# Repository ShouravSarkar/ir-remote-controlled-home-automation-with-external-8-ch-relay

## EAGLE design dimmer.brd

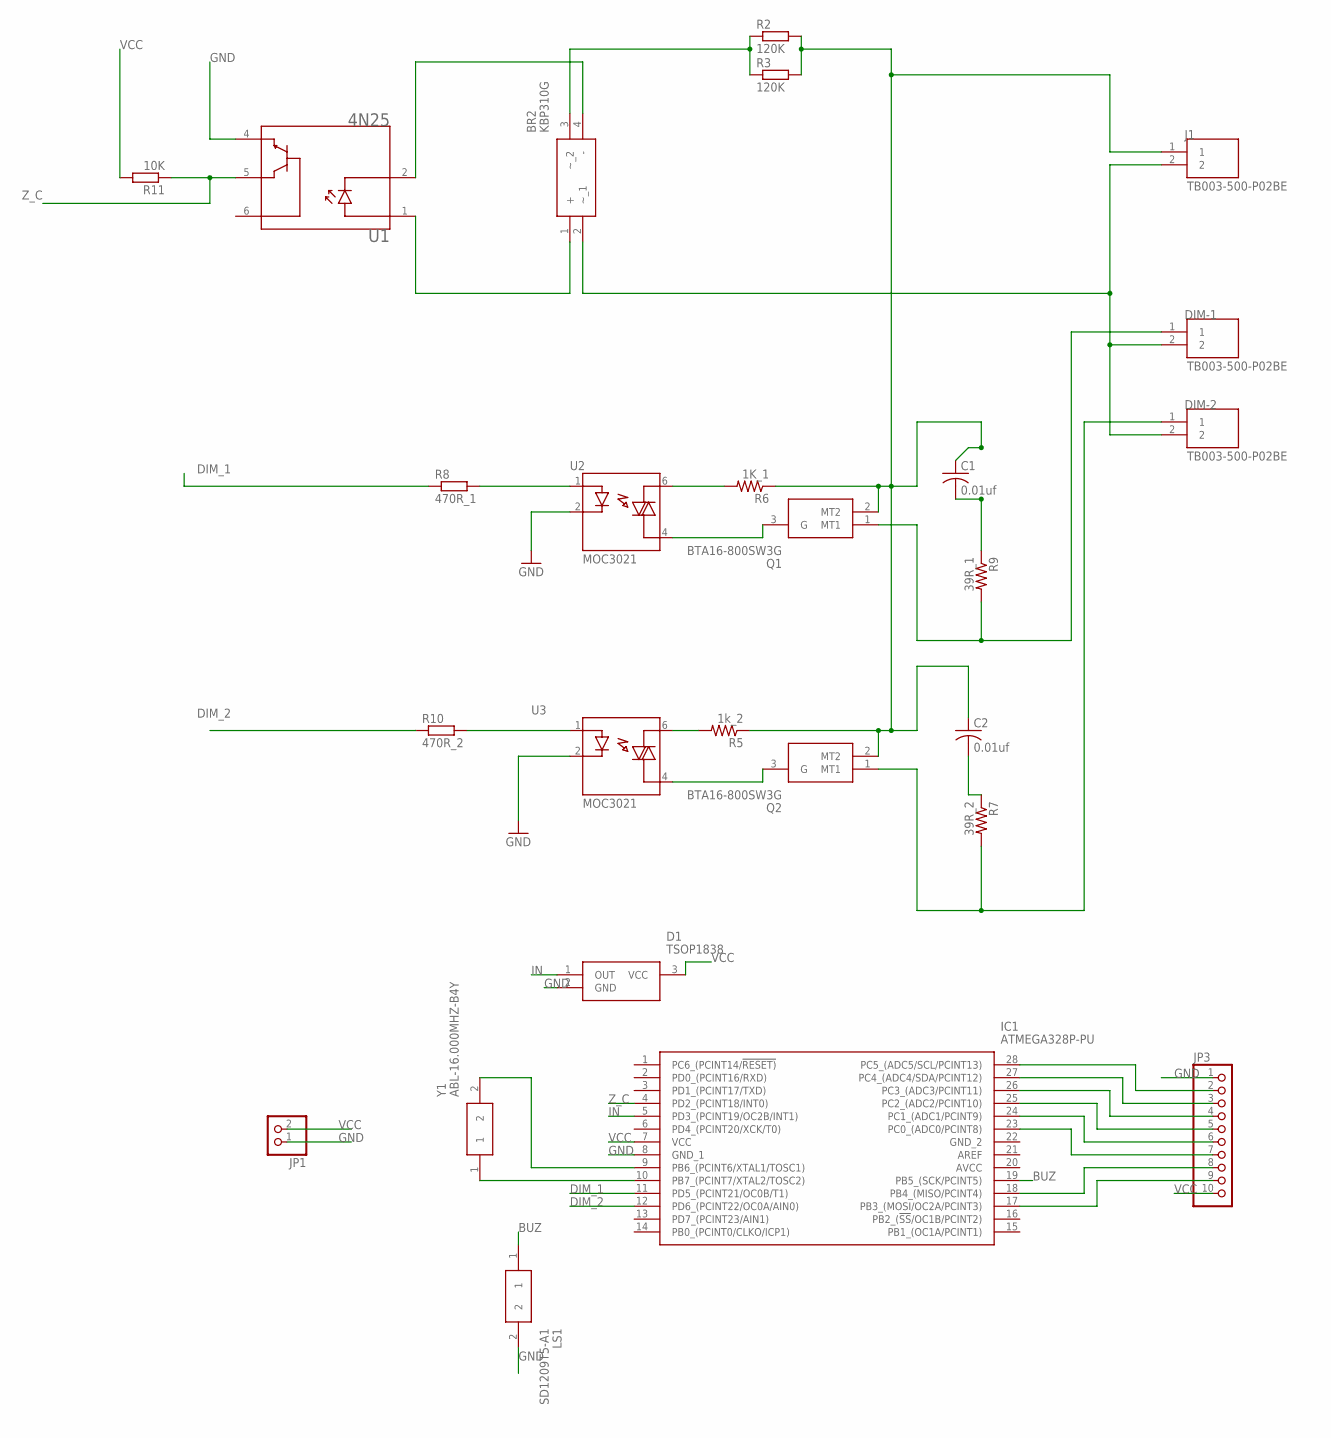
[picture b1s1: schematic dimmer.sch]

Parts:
BR2: KBP310G; TO385P508X1473X1168-4P
C1, C2: 0.01uf; C150-072X183
D1: TSOP1838; TSOP4856
DIM-1, DIM-2: TB003-500-P02BE; CUI_TB003-500-P02BE
IC1: ATMEGA328P-PU; DIP794W53P254L3467H457Q28N
J1: TB003-500-P02BE; CUI_TB003-500-P02BE
JP1: PINHD-1X2; 1X02
JP3: PINHD-1X10; 1X10
LS1: SD1209T5-A1
Q1, Q2: BTA16-800SW3G; TO254P482X997X2018-3P
R2, R3: 120K; 0617/22
R5: 1k_2; 0309/12
R6: 1K_1; 0309/12
R7: 39R_2; 0309/12
R8: 470R_1; 0207/10
R9: 39R_1; 0309/12
R10: 470R_2; 0207/10
R11: 10K; 0207/10
U1: 4N25; DIP762W50P254L712H400Q6N
U2, U3: MOC3021; DIP762W45P254L889H508Q6
Y1: ABL-16.000MHZ-B4Y; HC/49US_(AT49)PTH

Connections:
BUZ: IC1.19 (PB5_(SCK/PCINT5)), LS1.1
DIM_1: IC1.11 (PD5_(PCINT21/OC0B/T1)), R8.1
DIM_2: IC1.12 (PD6_(PCINT22/OC0A/AIN0)), R10.1
GND: D1.2 (GND), IC1.8 (GND_1), JP1.1, JP3.1, LS1.2, U1.4 (E), U2.2 (CATODE), U3.2 (CATODE)
IN: D1.1 (OUT), IC1.5 (PD3_(PCINT19/OC2B/INT1))
unnamed: BR2.4 (-), U1.2 (K)
unnamed: BR2.1 (+), U1.1 (A)
unnamed: BR2.3 (~_2), R2.1, R3.1
unnamed: R10.2, U3.1 (ANODE)
unnamed: C2.2, R7.1
unnamed: BR2.2 (~_1), DIM-1.2, DIM-2.2, J1.2
unnamed: IC1.9 (PB6_(PCINT6/XTAL1/TOSC1)), Y1.2
unnamed: C1.2, R9.1
unnamed: IC1.10 (PB7_(PCINT7/XTAL2/TOSC2)), Y1.1
unnamed: Q2.3 (G), U3.4 (MAIN_TERM2)
unnamed: Q1.3 (G), U2.4 (MAIN_TERM2)
unnamed: DIM-2.1, Q2.1 (MT1), R7.2
unnamed: DIM-1.1, Q1.1 (MT1), R9.2
unnamed: R8.2, U2.1 (ANODE)
unnamed: R5.2, U3.6 (MAIN_TERM1)
unnamed: R6.2, U2.6 (MAIN_TERM1)
unnamed: C1.1, C2.1, J1.1, Q1.2 (MT2), Q2.2 (MT2), R2.2, R3.2, R5.1, R6.1
unnamed: IC1.28 (PC5_(ADC5/SCL/PCINT13)), JP3.2
unnamed: IC1.27 (PC4_(ADC4/SDA/PCINT12)), JP3.3
unnamed: IC1.26 (PC3_(ADC3/PCINT11)), JP3.4
unnamed: IC1.25 (PC2_(ADC2/PCINT10)), JP3.5
unnamed: IC1.24 (PC1_(ADC1/PCINT9)), JP3.6
unnamed: IC1.23 (PC0_(ADC0/PCINT8)), JP3.7
unnamed: IC1.18 (PB4_(MISO/PCINT4)), JP3.8
unnamed: IC1.17 (PB3_(MOSI/OC2A/PCINT3)), JP3.9
VCC: D1.3 (VCC), IC1.7 (VCC), JP1.2, JP3.10, R11.2
Z_C: IC1.4 (PD2_(PCINT18/INT0)), R11.1, U1.5 (C)

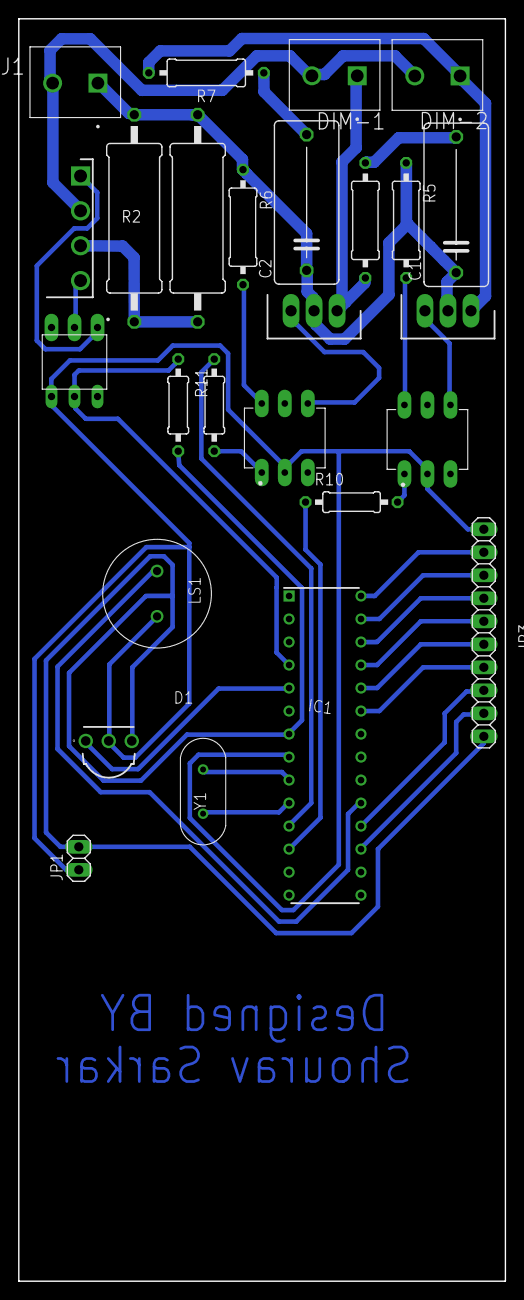
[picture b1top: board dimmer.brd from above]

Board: 2 copper layers, 53.7 x 139.3 mm, 26 parts (0 on the bottom side), 32 nets.

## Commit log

2020-05-20 for iqbal sir with 8 ch relay
